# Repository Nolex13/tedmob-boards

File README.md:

# Tedmob Boards

## Versions:
- Lumen: 3.2
- Pascal: 1.0

## Pascal
Vin: 24v

### 34v to 3.3v
Library: https://www.snapeda.com/parts/LM2596S-3.3/Texas%20Instruments/view-part/?welcome=home&t=LM2596S-3.3
Circuit explanation: https://www.eleccircuit.com/regulator-switching-dc-to-dc-step-down-voltage-with-lm2596/
C1: https://www.mouser.it/ProductDetail/EPCOS-TDK/B41866C5337M000?qs=sGAEpiMZZMsh%252B1woXyUXjwldr5%252B2pbyUhINvBs5L1LU%3D
DIODE: https://www.ebay.it/itm/323154064167?hash=item4b3d7bb327:g:0mUAAOSwv2taryM3
L1: https://www.mouser.it/ProductDetail/Murata-Electronics/LQM18DN330M70L?qs=aP1CjGhiNiFikTpZx0t6tA%3D%3D
C2: https://www.mouser.it/ProductDetail/Cornell-Dubilier-CDE/227SAK010M?qs=3tP%252BN51vMXcFP6ughiM38Q%3D%3D

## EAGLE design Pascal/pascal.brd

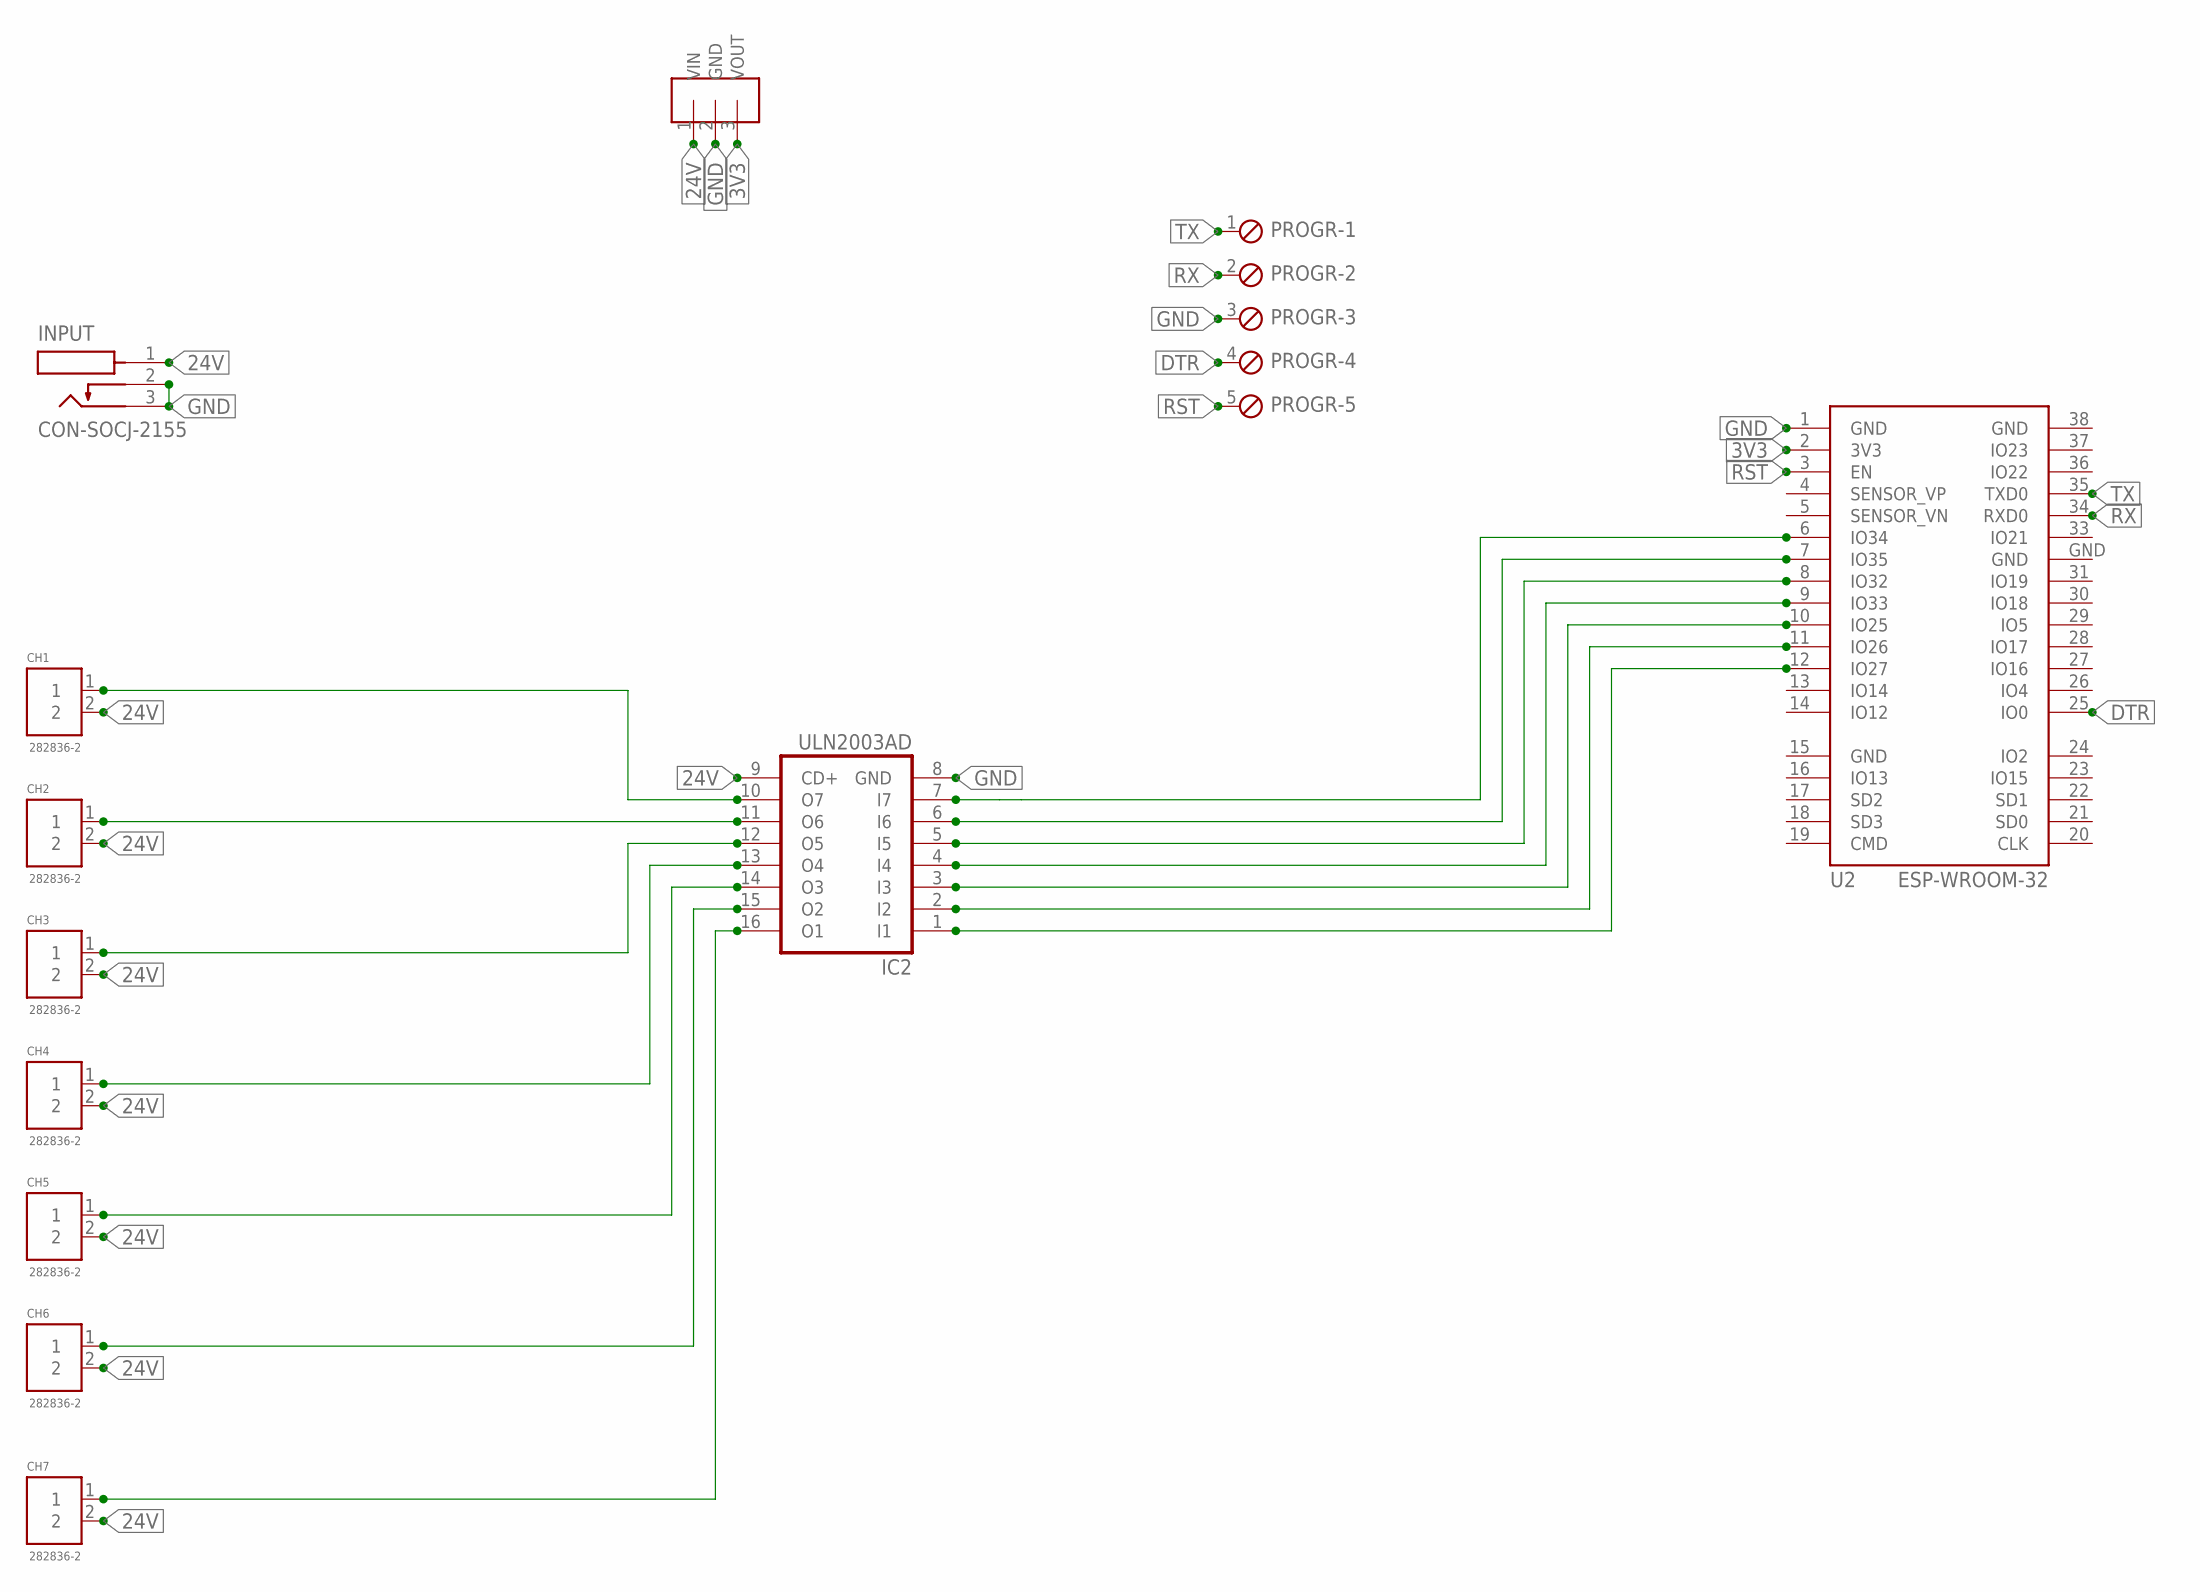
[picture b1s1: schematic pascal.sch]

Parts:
CH1, CH2, CH3, CH4, CH5, CH6, CH7: 282836-2; CONN_282836-2
IC2: ULN2003AD; SO16
INPUT: CON-SOCJ-2155; GRAVITECH_CON-SOCJ-2155
PROGR: MPT5; 5POL254
U2: ESP-WROOM-32
U$1: OKI-78SR-3.3/1.5; CONV_OKI-78SR-5/1.5-W36-C

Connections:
3V3: U2.2 (3V3), U$1.3 (VOUT)
24V: CH1.2, CH2.2, CH3.2, CH4.2, CH5.2, CH6.2, CH7.2, IC2.9 (CD+), INPUT.1, U$1.1 (VIN)
DTR: PROGR.4, U2.25 (IO0)
GND: IC2.8 (GND), INPUT.2, INPUT.3, PROGR.3, U2.1 (GND), U2.15 (GND), U2.38 (GND), U2.GND, U$1.2 (GND)
unnamed: IC2.7 (I7), U2.6 (IO34)
unnamed: IC2.6 (I6), U2.7 (IO35)
unnamed: IC2.5 (I5), U2.8 (IO32)
unnamed: CH3.1, IC2.12 (O5)
unnamed: CH1.1, IC2.10 (O7)
unnamed: CH2.1, IC2.11 (O6)
unnamed: CH4.1, IC2.13 (O4)
unnamed: CH5.1, IC2.14 (O3)
unnamed: CH6.1, IC2.15 (O2)
unnamed: CH7.1, IC2.16 (O1)
unnamed: IC2.4 (I4), U2.9 (IO33)
unnamed: IC2.3 (I3), U2.10 (IO25)
unnamed: IC2.2 (I2), U2.11 (IO26)
unnamed: IC2.1 (I1), U2.12 (IO27)
RST: PROGR.5, U2.3 (EN)
RX: PROGR.2, U2.34 (RXD0)
TX: PROGR.1, U2.35 (TXD0)

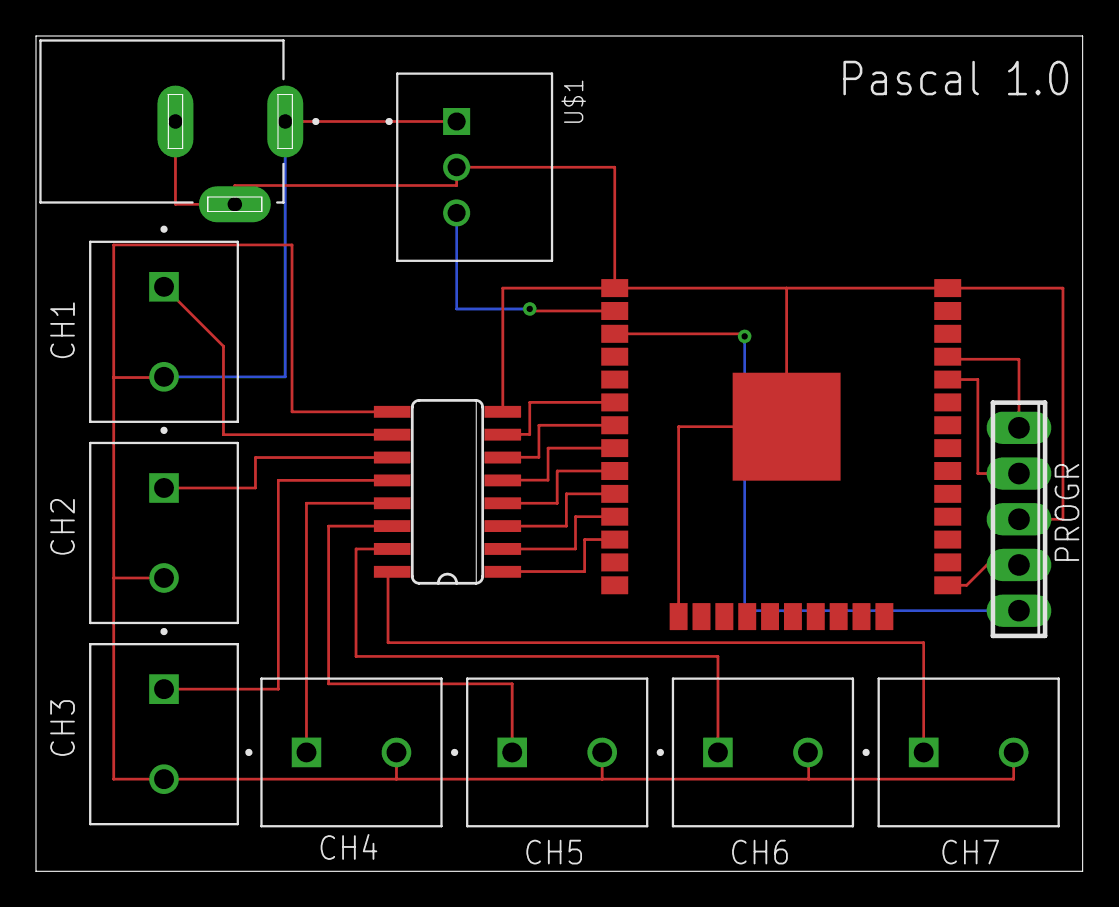
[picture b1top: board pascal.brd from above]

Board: 2 copper layers, 58.1 x 46.4 mm, 12 parts (0 on the bottom side), 21 nets.

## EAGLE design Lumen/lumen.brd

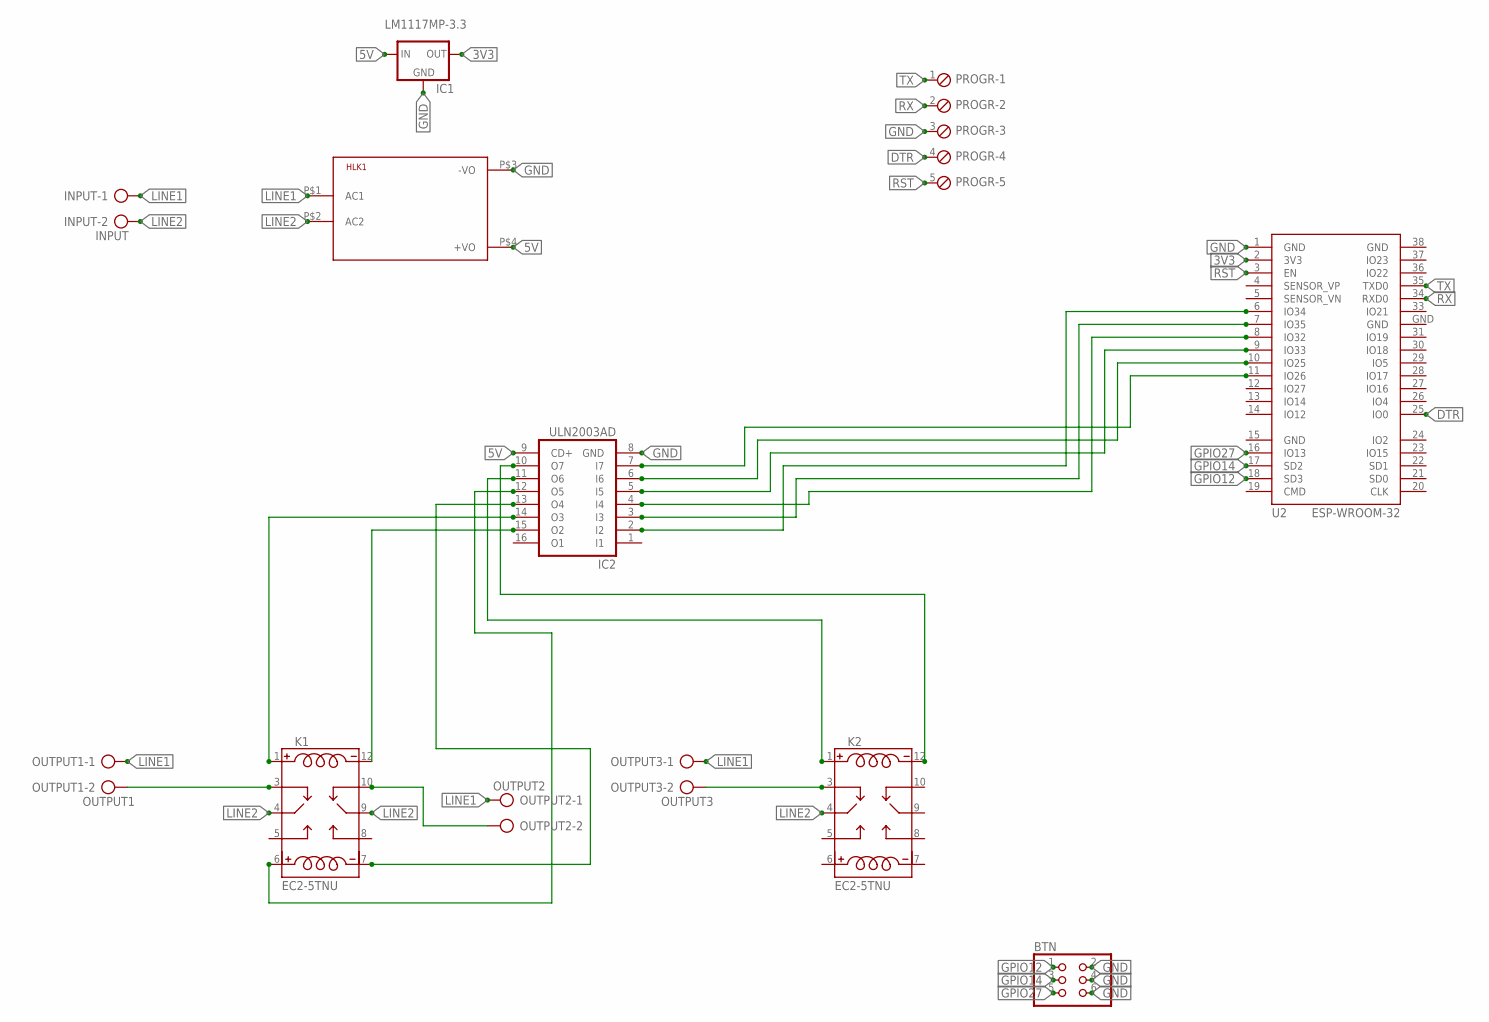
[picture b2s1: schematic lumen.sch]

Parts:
BTN: PINHD-2X3; 2X03
HLK1: HLK-PM013W; HLK-PM01
IC1: LM1117MP-3.3; SOT223
IC2: ULN2003AD; SO16
INPUT: INPUT; AK300/2
K1, K2: EC2-5TNU; RELAY_EC2-5TNU
OUTPUT1: OUTPUT1; AK300/2
OUTPUT2: OUTPUT2; AK300/2
OUTPUT3: OUTPUT3; AK300/2
PROGR: MPT5; 5POL254
U2: ESP-WROOM-32

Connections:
3V3: IC1.2 (OUT), IC1.4 (OUT), U2.2 (3V3)
5V: HLK1.P$4 (+VO), IC1.3 (IN), IC2.9 (CD+)
DTR: PROGR.4, U2.25 (IO0)
GND: BTN.2, BTN.4, BTN.6, HLK1.P$3 (-VO), IC1.1 (GND), IC2.8 (GND), PROGR.3, U2.1 (GND), U2.15 (GND), U2.38 (GND), U2.GND
GPIO12: BTN.1, U2.18 (SD3)
GPIO14: BTN.3, U2.17 (SD2)
GPIO27: BTN.5, U2.16 (IO13)
LINE1: HLK1.P$1 (AC1), INPUT.1, OUTPUT1.1, OUTPUT2.1, OUTPUT3.1
LINE2: HLK1.P$2 (AC2), INPUT.2, K1.4 (M1), K1.9 (M), K2.4 (M1)
unnamed: IC2.11 (O6), K2.1 (C1)
unnamed: K2.3 (NC1), OUTPUT3.2
unnamed: IC2.10 (O7), K2.12 (C2)
unnamed: IC2.15 (O2), K1.12 (C2)
unnamed: IC2.14 (O3), K1.1 (C1)
unnamed: K1.3 (NC1), OUTPUT1.2
unnamed: K1.10 (NC), OUTPUT2.2
unnamed: IC2.2 (I2), U2.6 (IO34)
unnamed: IC2.13 (O4), K1.7 (C4)
unnamed: IC2.12 (O5), K1.6 (C3)
unnamed: IC2.3 (I3), U2.7 (IO35)
unnamed: IC2.4 (I4), U2.8 (IO32)
unnamed: IC2.5 (I5), U2.9 (IO33)
unnamed: IC2.6 (I6), U2.10 (IO25)
unnamed: IC2.7 (I7), U2.11 (IO26)
RST: PROGR.5, U2.3 (EN)
RX: PROGR.2, U2.34 (RXD0)
TX: PROGR.1, U2.35 (TXD0)

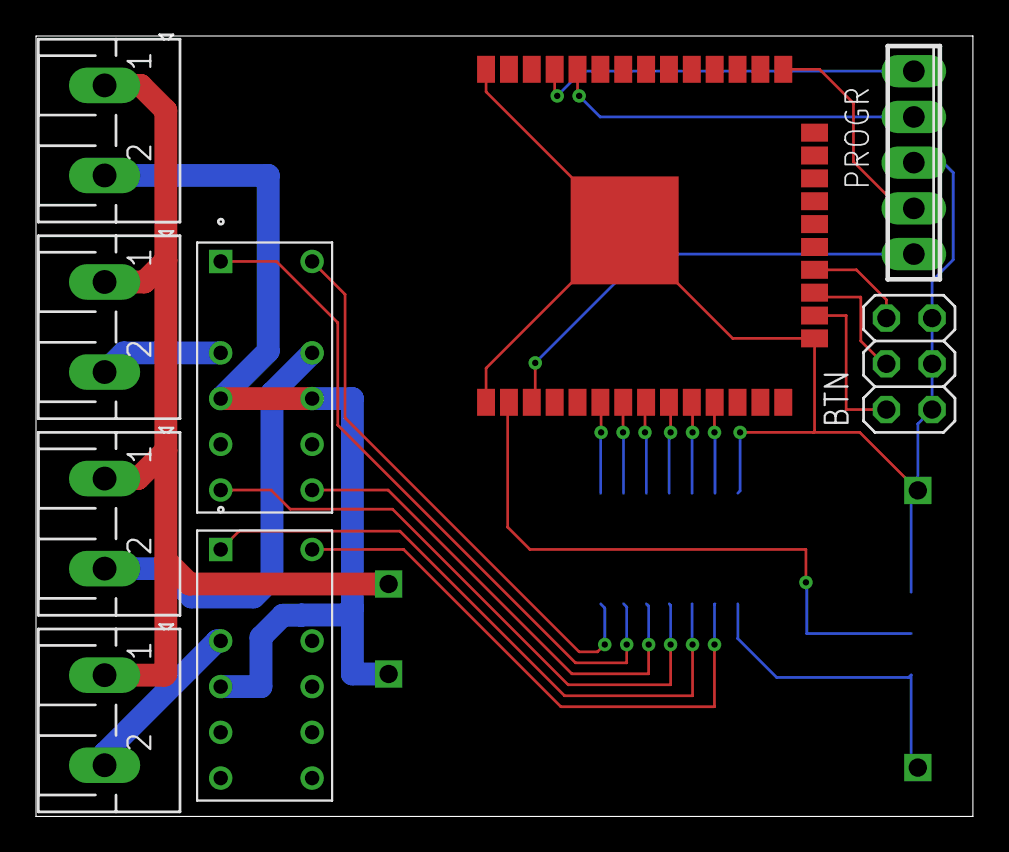
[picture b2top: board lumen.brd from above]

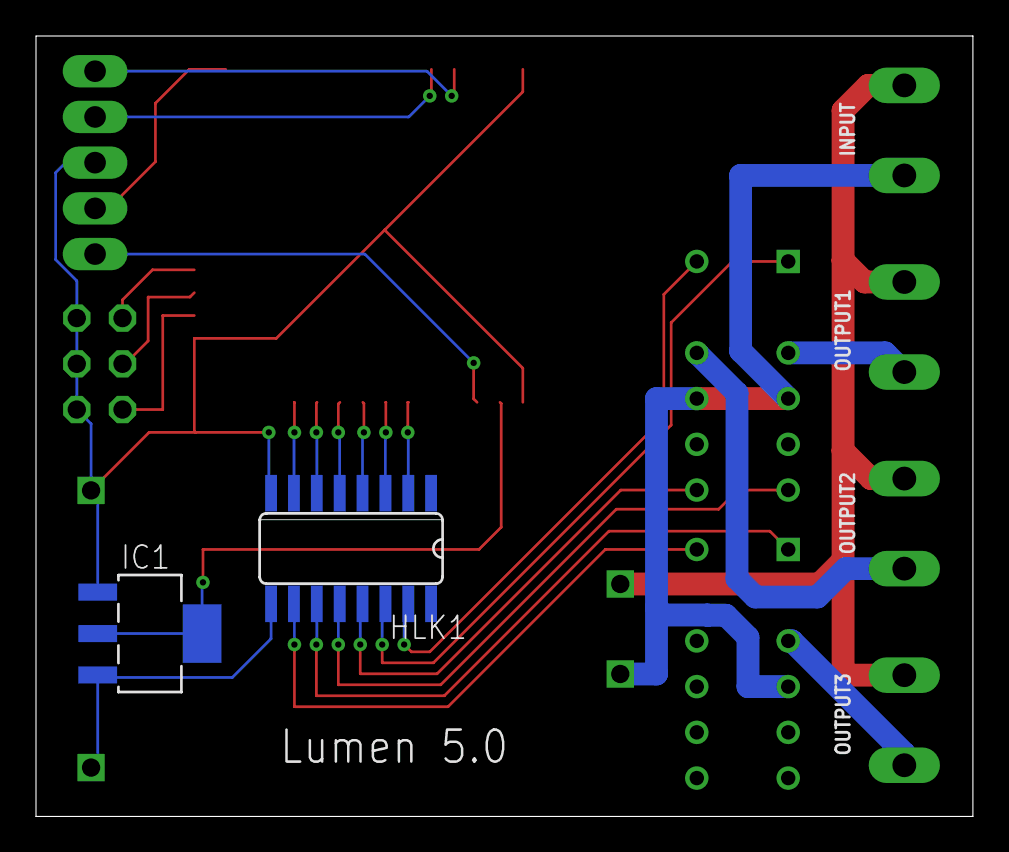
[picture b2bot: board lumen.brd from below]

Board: 2 copper layers, 52.1 x 43.4 mm, 12 parts (2 on the bottom side), 27 nets.

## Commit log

2022-04-11 Voltage regulator added to documentation
2022-04-11 remove ds store fails

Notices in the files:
parts and their libraries:
esp32: Creative Commons Attribution-ShareAlike 4.0 International
